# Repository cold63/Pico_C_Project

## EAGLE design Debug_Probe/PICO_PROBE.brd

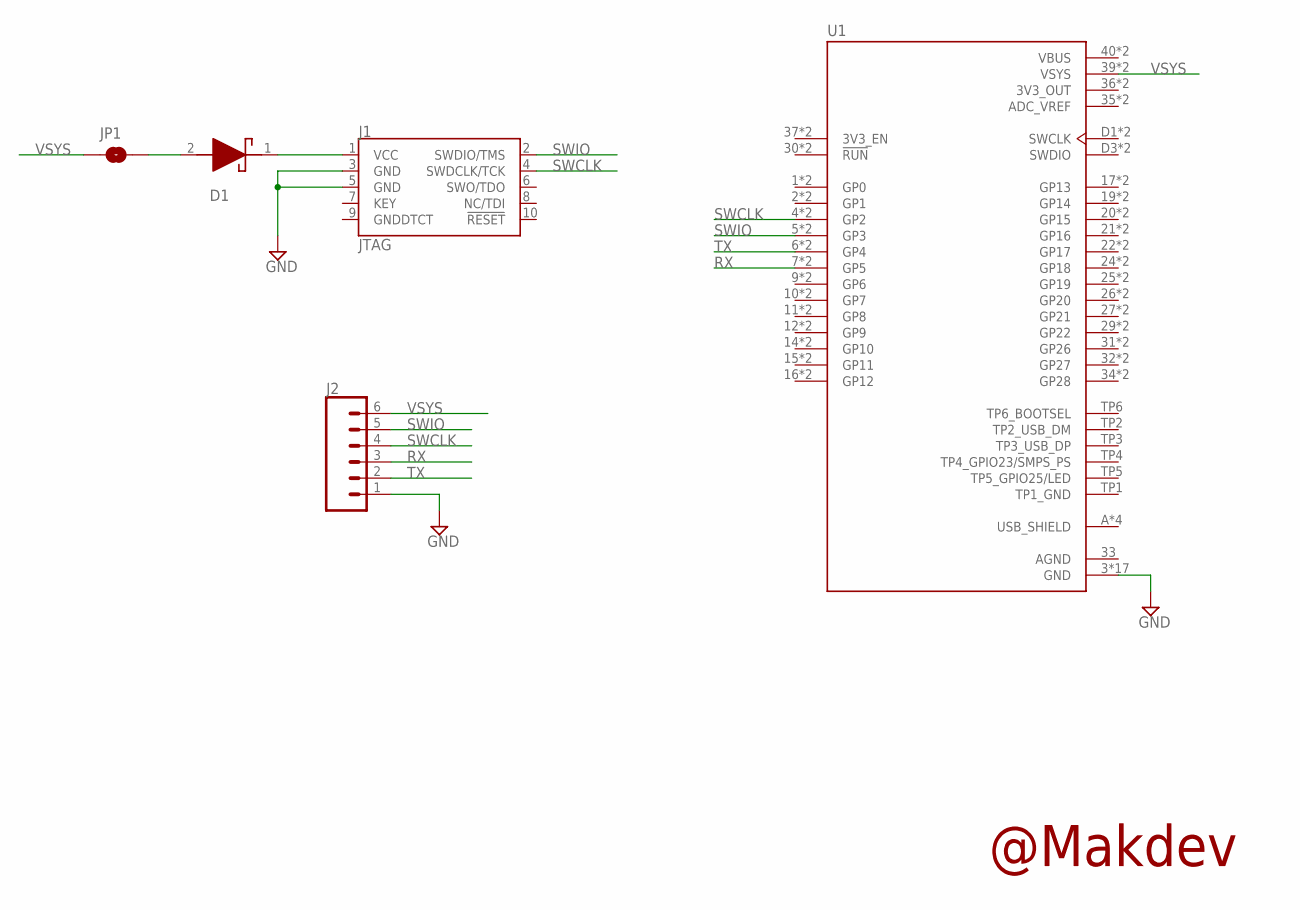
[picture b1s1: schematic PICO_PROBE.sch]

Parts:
D1: MBR120VLSFT1; SODFL3616X98N
J1: JTAG; 2X5-SMD-1.27MM
J2: CONN_06NO_SILK_FEMALE_PTH; 1X06_NO_SILK
JP1: JUMPER-SMT_2_NO_NO-SILK; SMT-JUMPER_2_NO_NO-SILK
U1: SC0915; MODULE_SC0915

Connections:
3V3_OUT: U1.36 (3V3_OUT), U1.36_36 (3V3_OUT)
ADC_VREF: U1.35 (ADC_VREF), U1.35_35 (ADC_VREF)
AGND: U1.33 (AGND)
GND: J1.3 (GND), J1.5 (GND), J2.1, U1.3 (GND), U1.3_3 (GND), U1.8 (GND), U1.8_8 (GND), U1.13 (GND), U1.13_13 (GND), U1.18 (GND), U1.18_18 (GND), U1.23 (GND), U1.23_23 (GND), U1.28 (GND), U1.28_28 (GND), U1.33_33 (GND), U1.38 (GND), U1.38_38 (GND), U1.D2 (GND), U1.D2_2 (GND)
unnamed: D1.2 (A), JP1.2
unnamed: D1.1 (K), J1.1 (VCC)
RX: J2.3, U1.7 (GP5), U1.7_7 (GP5)
SWCLK: J1.4 (SWDCLK/TCK), J2.4, U1.4 (GP2), U1.4_4 (GP2)
SWIO: J1.2 (SWDIO/TMS), J2.5, U1.5 (GP3), U1.5_5 (GP3)
TP1_GND: U1.TP1 (TP1_GND)
TX: J2.2, U1.6 (GP4), U1.6_6 (GP4)
USB_SHIELD: U1.A (USB_SHIELD), U1.B (USB_SHIELD), U1.C (USB_SHIELD), U1.D (USB_SHIELD)
VBUS: U1.40 (VBUS), U1.40_40 (VBUS)
VSYS: J2.6, JP1.1, U1.39 (VSYS), U1.39_39 (VSYS)

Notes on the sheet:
@Makdev

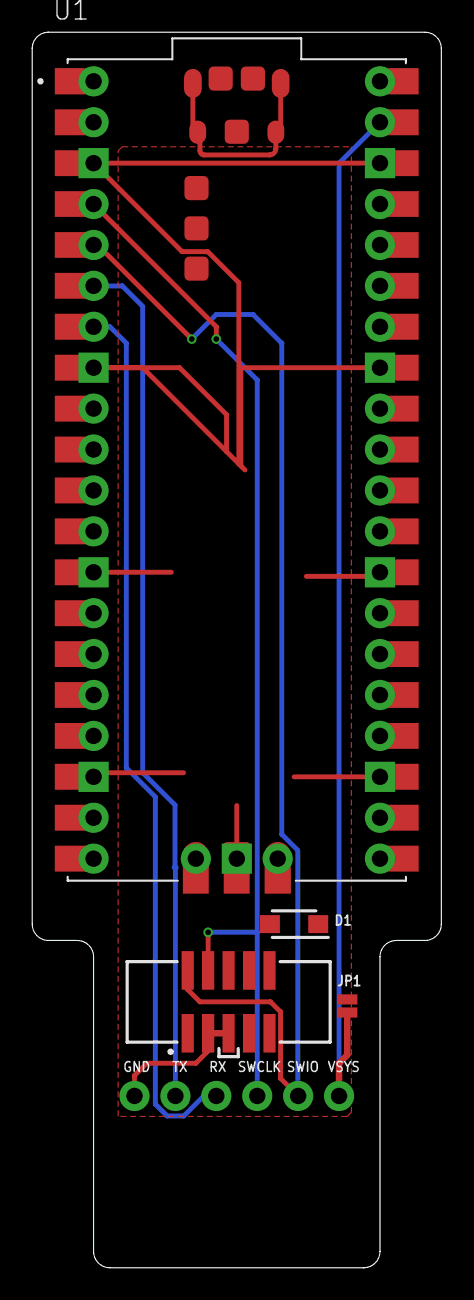
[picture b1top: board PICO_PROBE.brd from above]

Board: 2 copper layers, 25.4 x 76.7 mm, 6 parts (0 on the bottom side), 12 nets.

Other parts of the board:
U$1: PI-PICO-DEBUG-QRCODE

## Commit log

2022-08-19 add ultrasonic sensor hc-sr04
2022-08-29 Modify
2022-10-04 Debug probe

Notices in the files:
parts and their libraries:
SparkFun-Connectors: Licensing: Creative Commons ShareAlike 4.0 International - https://creativecommons.org/licenses/by-sa/4.0
